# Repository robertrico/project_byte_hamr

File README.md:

# Byte Hamr

An open-source FPGA expansion card for the Apple II family of computers.

## Overview

Byte Hamr brings modern FPGA capabilities to the Apple II, II+, IIe, and IIgs. Unlike purpose-built cards that serve a single function, Byte Hamr is a general-purpose platform for developing and running custom hardware designs on vintage Apple hardware.

The card sits between the simplicity of the A2FPGA (which targets HDMI output) and the complexity of the Carte Blanche (which is difficult to obtain and uses proprietary tooling). Byte Hamr uses the Lattice ECP5 FPGA with full support for the open-source Yosys/nextpnr toolchain.

## Features

- Lattice ECP5-85F FPGA (84K LUTs, BGA381 package)
- 64MB SDRAM (AS4C32M16SB-7TCNTR)
- 128Mb SPI Flash for bitstream storage
- USB programming via FTDI FT231XQ
- JTAG header for development/debugging
- 20-pin GPIO header with heavy ground interleaving (Rev 2)
- 2×3 power breakout: +3V3, +5V, −5V, +12V, −12V (Rev 2)
- Full Apple II bus interface with bidirectional level shifting
- Dedicated FPGA-controlled data-bus transceiver OE (Rev 2)
- Hardware R/W inverter for correct transceiver direction (Rev 2)
- Bidirectional nRES — drive *and* monitor Apple II reset (Rev 2)
- Dual power input (USB or Apple II bus) with automatic switching
- On-board 100 MHz oscillator (Rev 2; 25 MHz on Rev 1)
- Open-source hardware and gateware

## Specifications

| Parameter | Value |
|-----------|-------|
| FPGA | Lattice ECP5-85F (LFE5U-85F-8BG381I) |
| Logic Elements | 84K LUTs |
| Block RAM | 3744 Kbit |
| SDRAM | 64MB, 16-bit bus |
| Flash | 128Mb SPI |
| USB | Full-speed via FT231XQ |
| GPIO | 20 pins, 3.3V LVCMOS33 |
| Oscillator | 100 MHz (Rev 2) |
| Power | +5V from USB or Apple II slot |
| Dimensions | Standard Apple II card form factor |

## Architecture

```
                                    +------------------+
                                    |     SDRAM        |
                                    |   (64MB x16)     |
                                    +--------+---------+
                                             |
+-------------+     +----------+     +-------+--------+     +----------+
| Apple II    |     | Level    |     |                |     |   SPI    |
| Expansion   +---->+ Shifters +---->+   ECP5-85F     +---->+  Flash   |
| Slot        |     | (5V/3.3V)|     |     FPGA       |     |  (16MB)  |
+-------------+     +----------+     +-------+--------+     +----------+
                                             |
                                     +-------+--------+
                                     |      USB       |
                                     |  (FT231XQ)     |
                                     +----------------+
```

## Power Distribution

Three on-board switching regulators generate the required voltages:

- +3.3V for FPGA I/O, SDRAM, Flash, level shifters
- +2.5V for FPGA auxiliary power
- +1.1V for FPGA core

Power can be sourced from USB (+5V) or the Apple II slot, with Schottky diode OR-ing for automatic switching. Rev 2 moves the 5V input diode ahead of the level-shifter rail so USB alone can power the bus logic.

## Bus Interface

Six 74LVC8T245 bidirectional level shifters translate between the Apple II's 5V bus and the FPGA's 3.3V I/O. The interface provides access to:

- 16-bit address bus
- 8-bit data bus (bidirectional)
- Control signals (R/W, PHI0, device select, etc.)

Rev 2 adds a dedicated 74AHC1G04 inverter (`U7`) that generates the correct-polarity DIR control for the data-bus transceiver, and exposes the transceiver's OE on an FPGA pin so gateware can cleanly gate drive.

## GPIO Header

20-pin header with ground interleaving (pin `1` marked at the top, `20` at the bottom). All pins are 3.3V LVCMOS33.

| GPIO | FPGA Site |   | GPIO | FPGA Site |
|------|-----------|---|------|-----------|
| GPIO_1  | P3 |   | GPIO_11 | J1 |
| GPIO_2  | P1 |   | GPIO_12 | H2 |
| GPIO_3  | P2 |   | GPIO_13 | H1 |
| GPIO_4  | N1 |   | GPIO_14 | G2 |
| GPIO_5  | M1 |   | GPIO_15 | G1 |
| GPIO_6  | L2 |   | GPIO_16 | F2 |
| GPIO_7  | L1 |   | GPIO_17 | F1 |
| GPIO_8  | K3 |   | GPIO_18 | E2 |
| GPIO_9  | K1 |   | GPIO_19 | E1 |
| GPIO_10 | K2 |   | GPIO_20 | D2 |

See [byte_hamr.lpf](gateware/rev2/constraints/byte_hamr.lpf) for full pin constraints.

## Project Status

**Rev 2** — fabricated and bring-up in progress (April 2026). Both boards enumerate over USB and pass initial SDRAM + GPIO tests.

**Rev 1** — sent to fabrication (December 2025). Tagged `rev1` in git; all Rev 1 gateware preserved under `gateware/rev1/`.

See [VERSION.md](VERSION.md) for full version history.

### Rev 2 changes

- Board footprint shrunk
- GPIO expanded from 12 → 20 pins with dense ground interleaving
- Power breakout block exposing ±5V / ±12V / 3V3
- On-board R/W inverter (replaces Rev 1 bodge wire)
- 5V diode moved ahead of level shifters so USB can power the bus side
- Shortened SDRAM routes to the ECP5
- Data-bus transceiver OE promoted from GPIO bodge to dedicated FPGA pin (`DATA_OE`, B20)
- Bidirectional nRES: separate `nRES_READ` input (A5) so gateware can monitor Apple II reset
- Oscillator upgraded 25 MHz → 100 MHz for better CDC oversampling and PLL headroom

## Repository Structure

```
project_byte_hamr/
├── hardware/
│   └── byte_hamr/          # Main FPGA card
│       ├── kicad/          # KiCad schematic and PCB
│       ├── bom/            # Bill of materials
│       └── gerbers/        # Manufacturing files
├── gateware/
│   ├── rev1/               # Rev 1 designs (frozen, matches rev1 git tag)
│   │   ├── constraints/
│   │   ├── signal_check/
│   │   ├── sdram_test/
│   │   ├── sdram_bank/
│   │   ├── pattern_rom/
│   │   ├── logic_hamr/
│   │   ├── smart_hamr/
│   │   ├── block_hamr/
│   │   └── flash_hamr/
│   └── rev2/               # Rev 2 designs (porting in progress)
│       ├── constraints/
│       └── signal_check/
├── software/
│   ├── ASM/                # 6502 assembly source (Merlin32)
│   ├── LOGICHAMR/          # Logic analyzer disk contents
│   └── utils/              # Disk image utilities
└── docs/                   # Documentation
```

## Getting Started

### Prerequisites

**Gateware:**
- [oss-cad-suite](https://github.com/YosysHQ/oss-cad-suite-build) (recommended) or individual tools:
  - [Yosys](https://github.com/YosysHQ/yosys) (synthesis)
  - [nextpnr-ecp5](https://github.com/YosysHQ/nextpnr) (place and route)
  - [openFPGALoader](https://github.com/trabucayre/openFPGALoader) (programming)

**6502 Assembly:**
- [Merlin32](https://brutaldeluxe.fr/products/crossdevtools/merlin/) (cross-assembler)

**Disk Utilities:**
- [AppleCommander](https://applecommander.github.io/) (disk image manipulation)
- [ADTPro](https://adtpro.com/) (disk transfer to real hardware)
- Java runtime

### Building Gateware

Builds are selected by `DESIGN` and `REV`. `REV` defaults to `rev1`; set `REV=rev2` when targeting the current hardware.

```bash
make                                # Build default (REV=rev1, DESIGN=signal_check)
make DESIGN=xxx                     # Build specific design (rev1)
make DESIGN=xxx REV=rev2            # Build against Rev 2 pinout
make sim DESIGN=xxx REV=rev2        # Run simulation
make wave                           # Run simulation and open GTKWave
make help                           # Show all available targets
```

`b8008_hamr` lives under `gateware/rev2/` and always needs `REV=rev2`; it also
needs `fusesoc` installed and a sibling `intel-8008-vhdl` checkout
(`INTEL8008_DIR`, default `~/Development/intel-8008-vhdl`) to generate its
netlist at build time, e.g. `make DESIGN=b8008_hamr REV=rev2 bit`.

### Programming

```bash
make DESIGN=xxx REV=rev2 prog                         # Program via JTAG (volatile)
make DESIGN=xxx REV=rev2 prog-flash                   # Program SPI flash (persistent)
make DESIGN=xxx REV=rev2 prog-flash SERIAL=<FTDI_SN>  # Target a specific board
```

### Software Development Workflow

```
┌─────────────┐     ┌───────────────┐     ┌─────────────┐     ┌───────────┐
│  Merlin32   │────▶│ AppleCommander│────▶│   ADTPro    │────▶│ Apple IIe │
│  (assemble) │     │ (create .dsk) │     │  (transfer) │     │   (run)   │
└─────────────┘     └───────────────┘     └─────────────┘     └───────────┘
```

```bash
# 1. Edit source in software/LOGICHAMR/*.S

# 2. Assemble with Merlin32
make assemble ASM_SRC=software/LOGICHAMR/LOGIC.S

# 3. Create disk image (auto-copied to ADTPro disks folder)
make create-dsk DSK=LOGICHAMR

# 4. Transfer via ADTPro to real hardware

# 5. On Apple II: BRUN LOGIC
```

**Disk utilities:**
```bash
make extract-dsk DSK=file.dsk     # Extract files from disk image
make list-dsk                     # List disks in ADTPro folder
```

### Utility Commands

```bash
make pinout             # Regenerate FPGA pinout from schematics
make lpf                # Regenerate LPF constraints
make clean              # Remove build files
```

## Gateware Designs

Rev 1 versions (proven on Rev 1 hardware):

| Design | Description |
|--------|-------------|
| [signal_check](gateware/rev1/signal_check/SIGNAL_CHECK.md) | Board bring-up test (SDRAM, GPIO, bus monitor) |
| sdram_test | Register-driven SDRAM access from Apple II |
| [sdram_bank](gateware/rev1/sdram_bank/README.md) | SDRAM bank-switching controller |
| [pattern_rom](gateware/rev1/pattern_rom/README.md) | SDRAM-backed pattern ROM for display testing |
| [logic_hamr](gateware/rev1/logic_hamr/README.md) | 8-channel logic analyzer with HIRES display |
| [smart_hamr](gateware/rev1/smart_hamr/README.md) | SmartPort/IWM disk controller with ESP32 companion |
| [block_hamr](gateware/rev1/block_hamr/README.md) | ProDOS block device with SDRAM and SPI flash persistence |
| [flash_hamr](gateware/rev1/flash_hamr/) | SD card ProDOS block device (PicoRV32 + FatFS) |

Rev 2 port: `signal_check` ported and validated; other designs pending.

## Testing

Bringup sequence for new boards:

1. Visual inspection
2. Power rail verification (+5V, +3.3V, +2.5V, +1.1V)
3. USB enumeration (FTDI detection)
4. FPGA configuration with [signal_check](gateware/rev2/signal_check/)
5. Oscillator verification (100 MHz on scope; derived 25 MHz appears on SDRAM_CLK)
6. GPIO walk — watch walking 1s across `GPIO_9`..`GPIO_20`
7. Apple II bus communication (register loopback at $C0C0)
8. Data-bus transceiver + R/W inverter walk: `C0C0:01 → C0C0`, then `02`, `04`, … `80`
9. Full system integration

## Design References

This project builds on the work of others:

- [ULX3S](https://github.com/emard/ulx3s) - ECP5 reference design, power architecture
- [Xander's 8-bit fun](https://xjmaas.wordpress.com/my-apple-collection/apple-edge-connector-template-for-eagle/) - Apple II Edge Card Design
- [Understanding the Apple IIe](https://archive.org/details/understanding_the_apple_iie) - Jim Sather's essential reference

## Why "Byte Hamr"?

"Hamr" is Old Norse for "shape" or "form" — the concept of shapeshifting in Norse mythology. Byte Hamr: shapeshifting bytes. An FPGA that can become any hardware you define. The shape changes based on what you program it to be.

## License

This project is released under the [MIT License](LICENSE.md).

## Author

Robert Rico

## Contributing

This is an early-stage project. Issues, suggestions, and pull requests welcome.

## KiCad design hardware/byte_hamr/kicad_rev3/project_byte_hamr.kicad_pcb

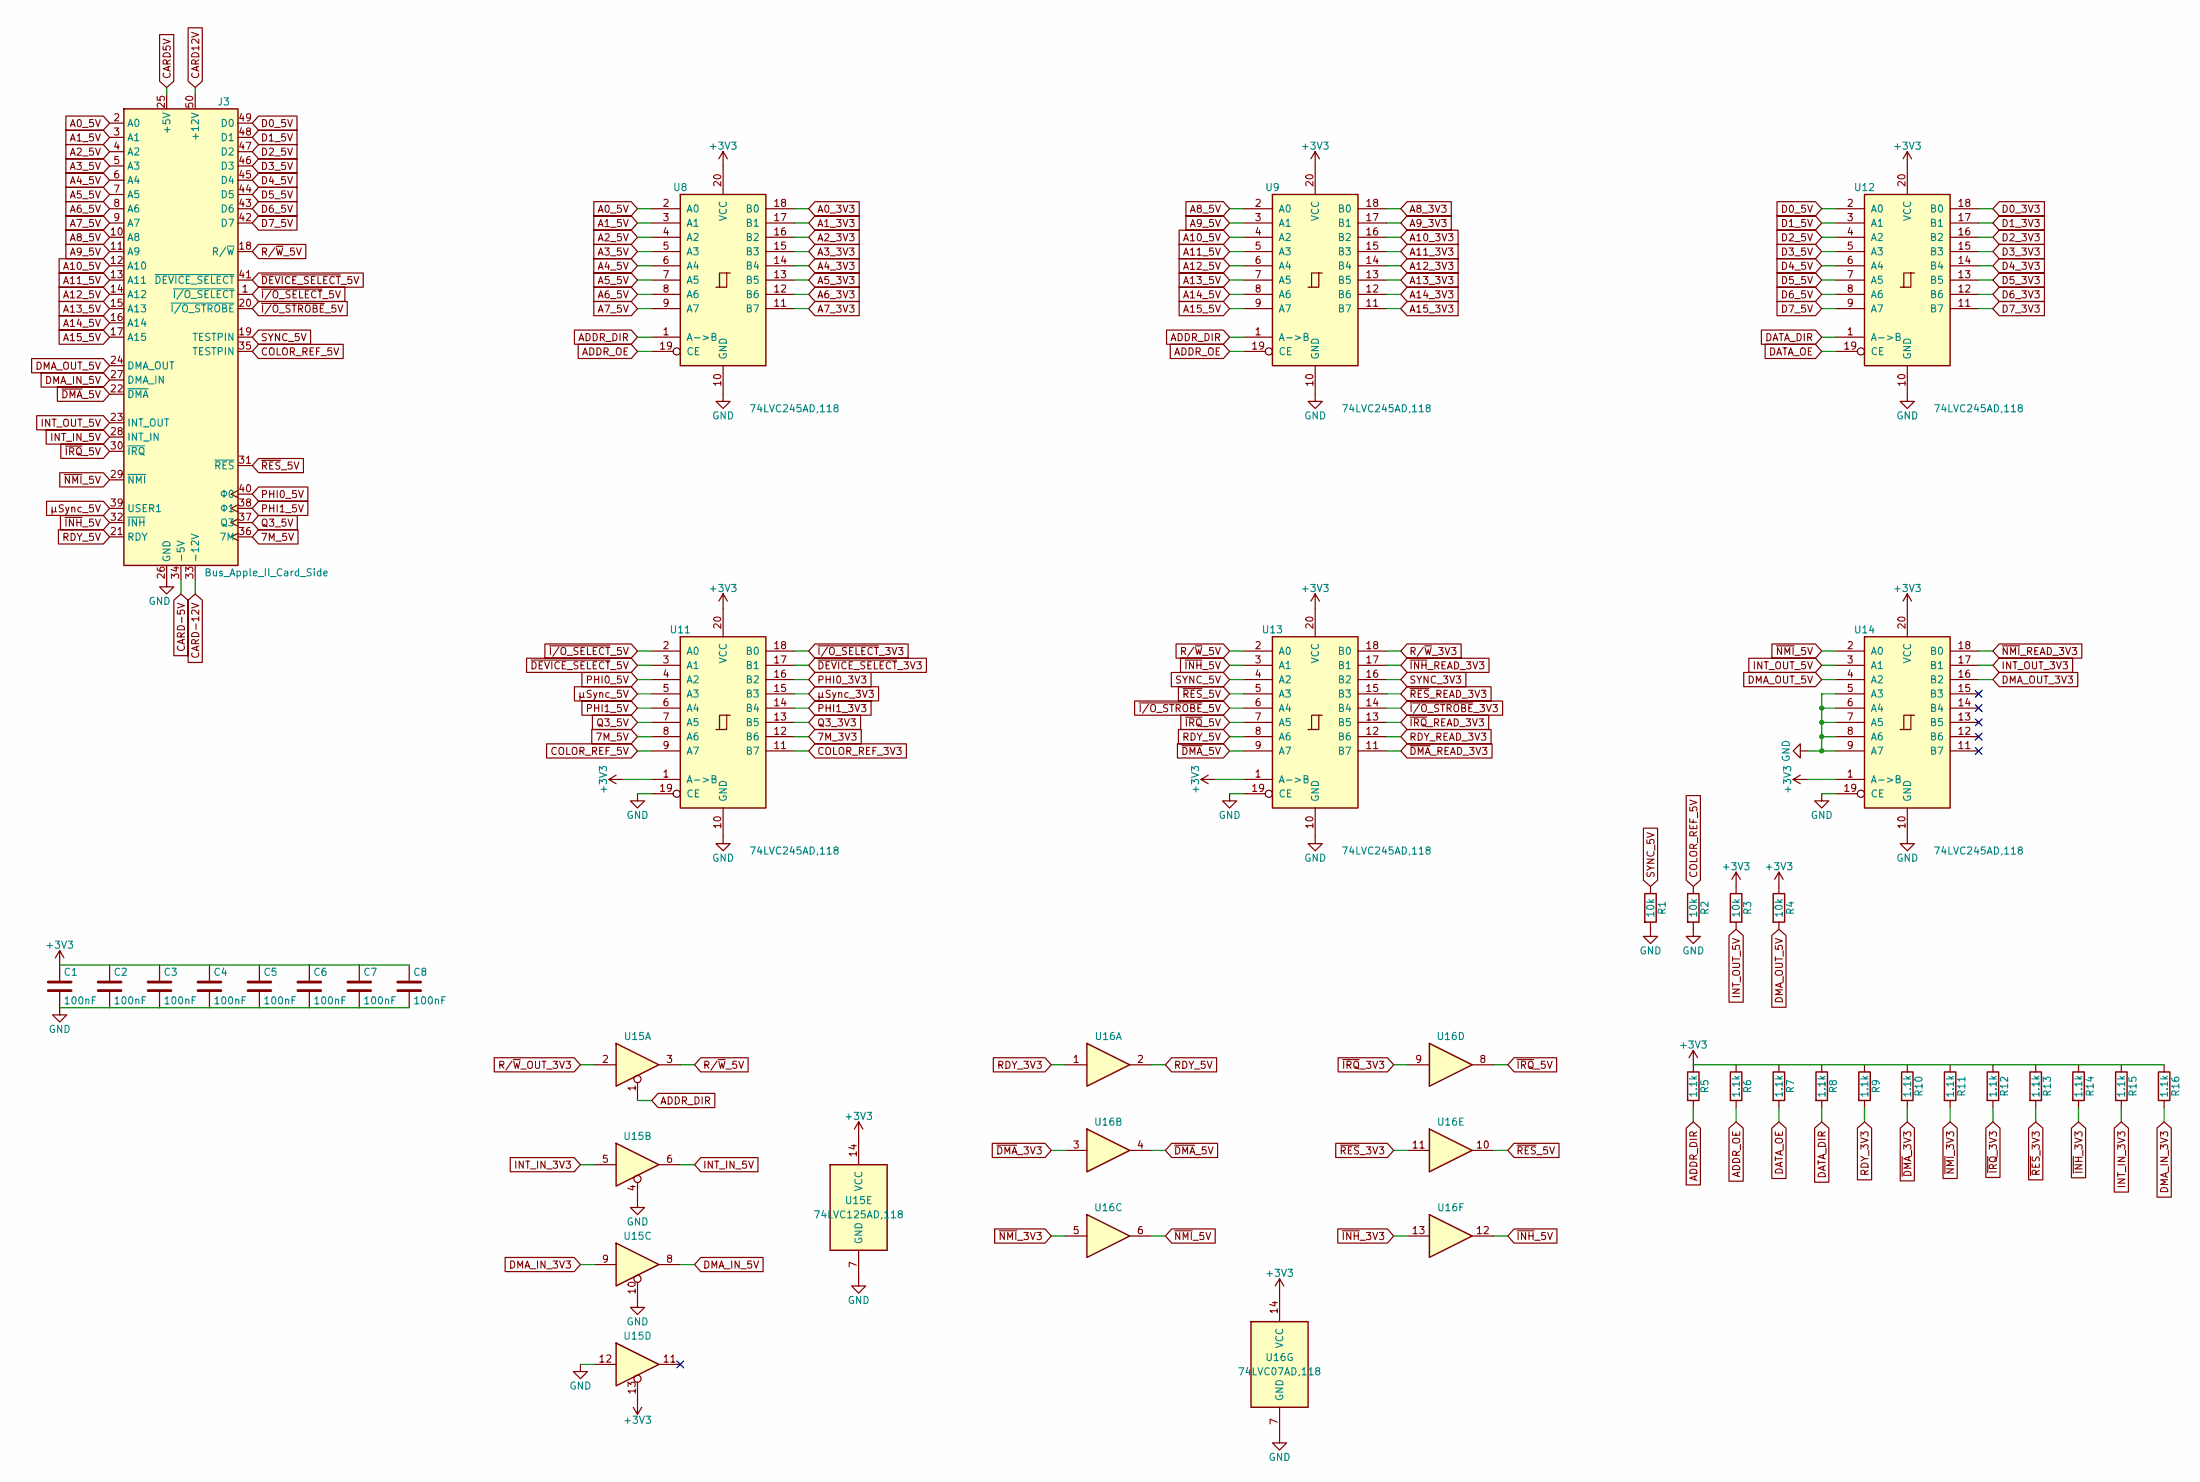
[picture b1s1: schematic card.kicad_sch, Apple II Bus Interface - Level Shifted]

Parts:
C1, C2, C3, C4, C5, C6, C7, C8: 100nF; C_1206_3216Metric; MPN CL31B104KBCNNNC; DigiKey 1276-1017-1-ND
J3: Bus_Apple_II_Card_Side; Peripheral_Bus_Edge
R1, R2, R3, R4: 10k; R_1206_3216Metric; MPN RMCF1206FT10K0; DigiKey RMCF1206FT10K0CT-ND
R5, R6, R7, R8, R9, R10, R11, R12, R13, R14, R15, R16: 1.1k; R_1206_3216Metric; MPN RMCF1206FT1K10; DigiKey 738-RMCF1206FT1K10CT-ND
U8, U9, U11, U12, U13, U14: 74LVC245AD,118; SOIC-20W_7.5x12.8mm_P1.27mm; MPN 74LVC245AD,118; DigiKey 1727-3104-1-ND
U15: 74LVC125AD,118; SOIC-14_3.9x8.7mm_P1.27mm; MPN 74LVC125AD,118; DigiKey 1727-3091-1-ND
U16: 74LVC07AD,118; SOIC-14_3.9x8.7mm_P1.27mm; MPN 74LVC07AD,118; DigiKey 1727-3089-1-ND

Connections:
7M_3V3: U11.12 (B6); also elsewhere on the board
7M_5V: J3.36 (7M), U11.8 (A6)
+3V3: C1.1, C2.1, C3.1, C4.1, C5.1, C6.1, C7.1, C8.1, R3.1, R4.1, R5.1, R6.1, R7.1, R8.1, R9.1, R10.1, R11.1, R12.1, R13.1, R14.1, R15.1, R16.1, U8.20 (VCC), U9.20 (VCC), U11.1 (A->B), U11.20 (VCC), U12.20 (VCC), U13.1 (A->B), U13.20 (VCC), U14.1 (A->B), U14.20 (VCC), U15.13, U15.14 (VCC), U16.14 (VCC); also elsewhere on the board
A0_3V3: U8.18 (B0); also elsewhere on the board
A0_5V: J3.2 (A0), U8.2 (A0)
A1_3V3: U8.17 (B1); also elsewhere on the board
A1_5V: J3.3 (A1), U8.3 (A1)
A2_3V3: U8.16 (B2); also elsewhere on the board
A2_5V: J3.4 (A2), U8.4 (A2)
A3_3V3: U8.15 (B3); also elsewhere on the board
A3_5V: J3.5 (A3), U8.5 (A3)
A4_3V3: U8.14 (B4); also elsewhere on the board
A4_5V: J3.6 (A4), U8.6 (A4)
A5_3V3: U8.13 (B5); also elsewhere on the board
A5_5V: J3.7 (A5), U8.7 (A5)
A6_3V3: U8.12 (B6); also elsewhere on the board
A6_5V: J3.8 (A6), U8.8 (A6)
A7_3V3: U8.11 (B7); also elsewhere on the board
A7_5V: J3.9 (A7), U8.9 (A7)
A8_3V3: U9.18 (B0); also elsewhere on the board
A8_5V: J3.10 (A8), U9.2 (A0)
A9_3V3: U9.17 (B1); also elsewhere on the board
A9_5V: J3.11 (A9), U9.3 (A1)
A10_3V3: U9.16 (B2); also elsewhere on the board
A10_5V: J3.12 (A10), U9.4 (A2)
A11_3V3: U9.15 (B3); also elsewhere on the board
A11_5V: J3.13 (A11), U9.5 (A3)
A12_3V3: U9.14 (B4); also elsewhere on the board
A12_5V: J3.14 (A12), U9.6 (A4)
A13_3V3: U9.13 (B5); also elsewhere on the board
A13_5V: J3.15 (A13), U9.7 (A5)
A14_3V3: U9.12 (B6); also elsewhere on the board
A14_5V: J3.16 (A14), U9.8 (A6)
A15_3V3: U9.11 (B7); also elsewhere on the board
A15_5V: J3.17 (A15), U9.9 (A7)
ADDR_DIR: R5.2, U8.1 (A->B), U9.1 (A->B), U15.1; also elsewhere on the board
ADDR_OE: R6.2, U8.19 (CE), U9.19 (CE); also elsewhere on the board
CARD5V: J3.25 (+5V); also elsewhere on the board
CARD12V: J3.50 (+12V); also elsewhere on the board
CARD-5V: J3.34 (-5V); also elsewhere on the board
CARD-12V: J3.33 (-12V); also elsewhere on the board
COLOR_REF_3V3: U11.11 (B7); also elsewhere on the board
COLOR_REF_5V: J3.35 (TESTPIN), R2.1, U11.9 (A7)
D0_3V3: U12.18 (B0); also elsewhere on the board
D0_5V: J3.49 (D0), U12.2 (A0)
D1_3V3: U12.17 (B1); also elsewhere on the board
D1_5V: J3.48 (D1), U12.3 (A1)
D2_3V3: U12.16 (B2); also elsewhere on the board
D2_5V: J3.47 (D2), U12.4 (A2)
D3_3V3: U12.15 (B3); also elsewhere on the board
D3_5V: J3.46 (D3), U12.5 (A3)
D4_3V3: U12.14 (B4); also elsewhere on the board
D4_5V: J3.45 (D4), U12.6 (A4)
D5_3V3: U12.13 (B5); also elsewhere on the board
D5_5V: J3.44 (D5), U12.7 (A5)
D6_3V3: U12.12 (B6); also elsewhere on the board
D6_5V: J3.43 (D6), U12.8 (A6)
D7_3V3: U12.11 (B7); also elsewhere on the board
D7_5V: J3.42 (D7), U12.9 (A7)
DATA_DIR: R8.2, U12.1 (A->B); also elsewhere on the board
DATA_OE: R7.2, U12.19 (CE); also elsewhere on the board
DMA_IN_3V3: R16.2, U15.9; also elsewhere on the board
DMA_IN_5V: J3.27 (DMA_IN), U15.8
DMA_OUT_3V3: U14.16 (B2); also elsewhere on the board
DMA_OUT_5V: J3.24 (DMA_OUT), R4.2, U14.4 (A2)
GND: C1.2, C2.2, C3.2, C4.2, C5.2, C6.2, C7.2, C8.2, J3.26 (GND), R1.2, R2.2, U8.10 (GND), U9.10 (GND), U11.10 (GND), U11.19 (CE), U12.10 (GND), U13.10 (GND), U13.19 (CE), U14.5 (A3), U14.6 (A4), U14.7 (A5), U14.8 (A6), U14.9 (A7), U14.10 (GND), U14.19 (CE), U15.4, U15.7 (GND), U15.10, U15.12, U16.7 (GND); also elsewhere on the board
INT_IN_3V3: R15.2, U15.5; also elsewhere on the board
INT_IN_5V: J3.28 (INT_IN), U15.6
INT_OUT_3V3: U14.17 (B1); also elsewhere on the board
INT_OUT_5V: J3.23 (INT_OUT), R3.2, U14.3 (A1)
PHI0_3V3: U11.16 (B2); also elsewhere on the board
PHI0_5V: J3.40 (Φ0), U11.4 (A2)
PHI1_3V3: U11.14 (B4); also elsewhere on the board
PHI1_5V: J3.38 (Φ1), U11.6 (A4)
Q3_3V3: U11.13 (B5); also elsewhere on the board
Q3_5V: J3.37 (Q3), U11.7 (A5)
RDY_3V3: R9.2, U16.1; also elsewhere on the board
RDY_5V: J3.21 (RDY), U13.8 (A6), U16.2
RDY_READ_3V3: U13.12 (B6); also elsewhere on the board
R/~W_3V3: U13.18 (B0); also elsewhere on the board
R/~W_5V: J3.18 (R/~W), U13.2 (A0), U15.3
R/~W_OUT_3V3: U15.2; also elsewhere on the board
SYNC_3V3: U13.16 (B2); also elsewhere on the board
SYNC_5V: J3.19 (TESTPIN), R1.1, U13.4 (A2)
~DEVICE_SELECT_3V3: U11.17 (B1); also elsewhere on the board
~DEVICE_SELECT_5V: J3.41 (~DEVICE_SELECT), U11.3 (A1)
~DMA_3V3: R10.2, U16.3; also elsewhere on the board
~DMA_5V: J3.22 (~DMA), U13.9 (A7), U16.4
~DMA_READ_3V3: U13.11 (B7); also elsewhere on the board
~INH_3V3: R14.2, U16.13; also elsewhere on the board
~INH_5V: J3.32 (~INH), U13.3 (A1), U16.12
~INH_READ_3V3: U13.17 (B1); also elsewhere on the board
~IRQ_3V3: R12.2, U16.9; also elsewhere on the board
~IRQ_5V: J3.30 (~IRQ), U13.7 (A5), U16.8
~IRQ_READ_3V3: U13.13 (B5); also elsewhere on the board
~I/O_SELECT_3V3: U11.18 (B0); also elsewhere on the board
~I/O_SELECT_5V: J3.1 (~I/O_SELECT), U11.2 (A0)
~I/O_STROBE_3V3: U13.14 (B4); also elsewhere on the board
~I/O_STROBE_5V: J3.20 (~I/O_STROBE), U13.6 (A4)
~NMI_3V3: R11.2, U16.5; also elsewhere on the board
~NMI_5V: J3.29 (~NMI), U14.2 (A0), U16.6
~NMI_READ_3V3: U14.18 (B0); also elsewhere on the board
~RES_3V3: R13.2, U16.11; also elsewhere on the board
~RES_5V: J3.31 (~RES), U13.5 (A3), U16.10
~RES_READ_3V3: U13.15 (B3); also elsewhere on the board
µSync_3V3: U11.15 (B3); also elsewhere on the board
µSync_5V: J3.39 (USER1), U11.5 (A3)

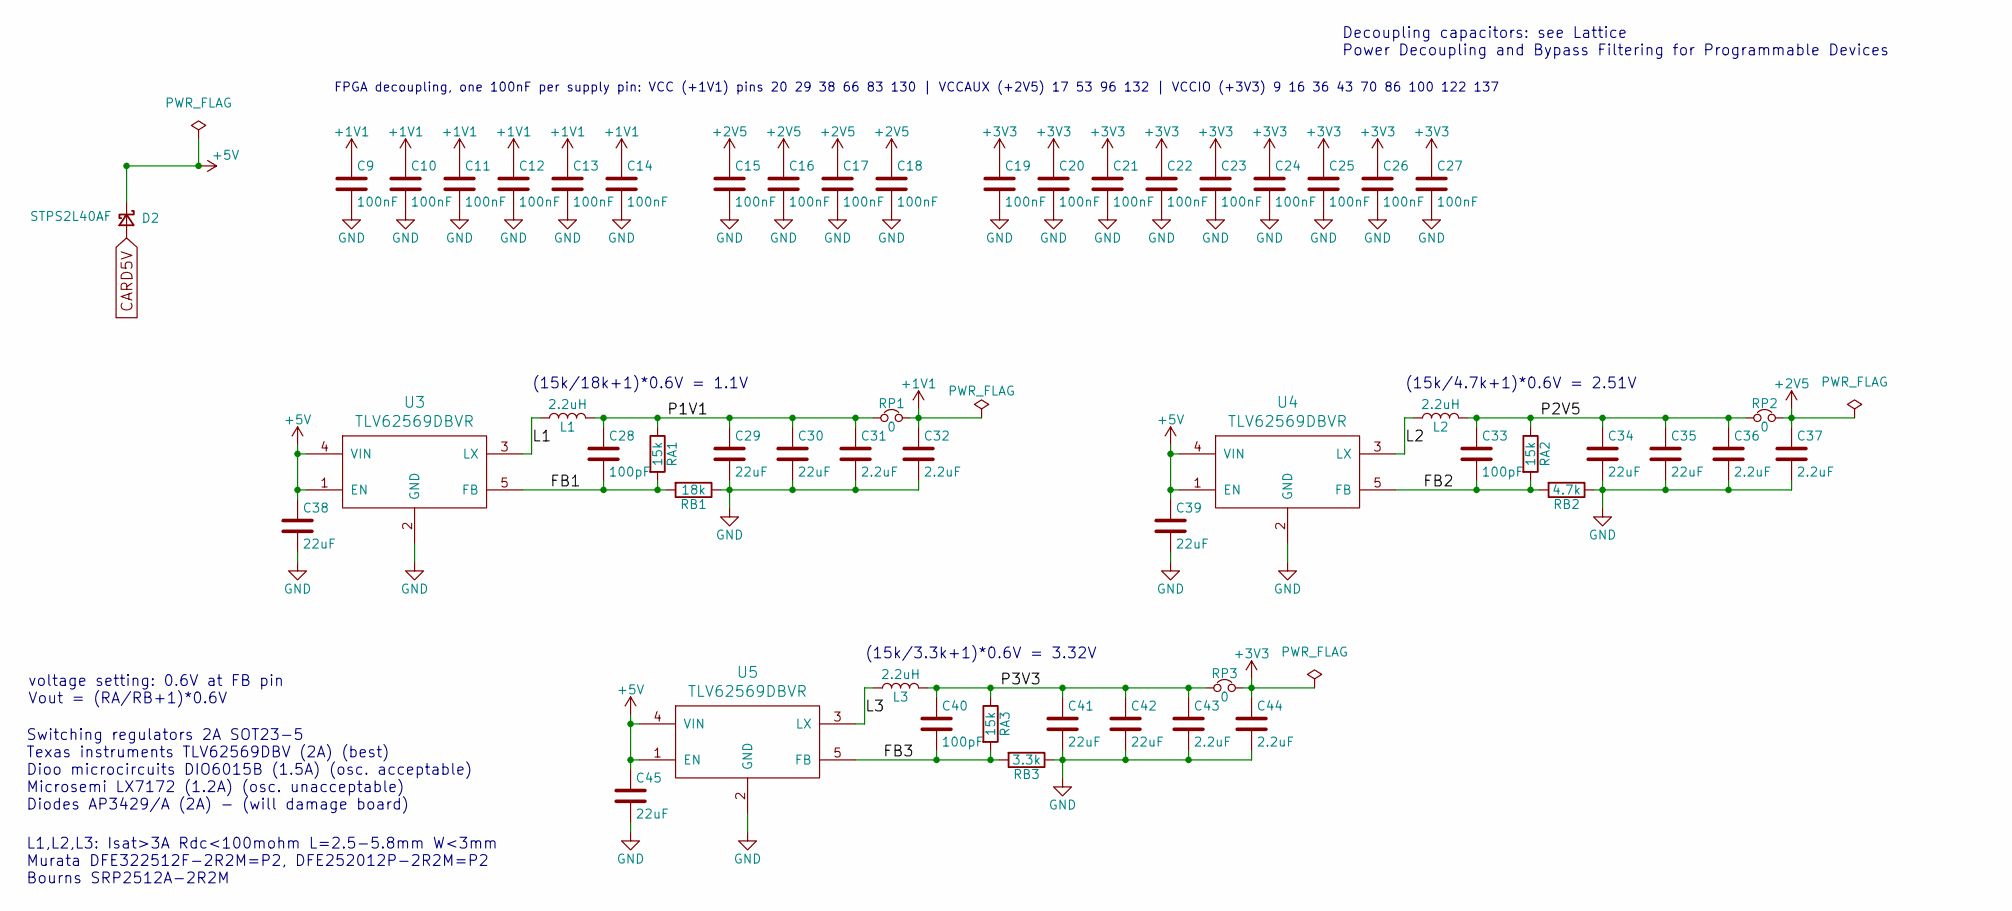
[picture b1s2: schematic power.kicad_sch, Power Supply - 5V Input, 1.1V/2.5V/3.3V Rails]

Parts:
C9, C10, C11, C12, C13, C14, C15, C16, C17, C18, C19, C20, C21, C22, C23, C24, C25, C26, C27: 100nF; C_1206_3216Metric; MPN CL31B104KBCNNNC; DigiKey 1276-1017-1-ND
C28, C33, C40: 100pF; C_1206_3216Metric; MPN 885012008043; DigiKey 732-7887-1-ND
C29, C30, C34, C35, C38, C39, C41, C42, C45: 22uF; C_1206_3216Metric; MPN CL31A226MOHNNNE; DigiKey 1276-3050-1-ND
C31, C32, C36, C37, C43, C44: 2.2uF; C_1206_3216Metric; MPN CL31B225KOHNNNE; DigiKey 1276-1264-1-ND
D2: STPS2L40AF; D_SMA; MPN STPS2L40AF; DigiKey 497-18870-1-ND
L1, L2, L3: 2.2uH; L_1008_1210; MPN DFE322520F-2R2M=P2; DigiKey 490-DFE322520F-2R2M=P2CT-ND
RA1, RA2, RA3: 15k; R_1206_3216Metric; MPN RMCF1206FT15K0; DigiKey RMCF1206FT15K0CT-ND
RB1: 18k; R_1206_3216Metric; MPN CR1206-FX-1802ELF; DigiKey CR1206-FX-1802ELFCT-ND
RB2: 4.7k; R_1206_3216Metric; MPN RMCF1206FT4K70; DigiKey RMCF1206FT4K70CT-ND
RB3: 3.3k; R_1206_3216Metric; MPN RMCF1206FT3K30; DigiKey RMCF1206FT3K30CT-ND
RP1, RP2, RP3: 0; R_1206_3216Metric; MPN RMCF1206ZT0R00; DigiKey RMCF1206ZT0R00CT-ND
U3, U4, U5: TLV62569DBVR; TSOT-25; MPN TLV62569DBVR; DigiKey 296-47360-1-ND

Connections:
+1V1: C9.1, C10.1, C11.1, C12.1, C13.1, C14.1, C32.1, RP1.2; also elsewhere on the board
+2V5: C15.1, C16.1, C17.1, C18.1, C37.1, RP2.2; also elsewhere on the board
+3V3: C19.1, C20.1, C21.1, C22.1, C23.1, C24.1, C25.1, C26.1, C27.1, C44.1, RP3.2; also elsewhere on the board
+5V: C38.1, C39.1, C45.1, D2.1 (K), U3.1 (EN), U3.4 (VIN), U4.1 (EN), U4.4 (VIN), U5.1 (EN), U5.4 (VIN)
/power/FB1: C28.2, RA1.2, RB1.2, U3.5 (FB)
/power/FB2: C33.2, RA2.2, RB2.2, U4.5 (FB)
/power/FB3: C40.2, RA3.2, RB3.2, U5.5 (FB)
/power/L1: L1.1, U3.3 (LX)
/power/L2: L2.1, U4.3 (LX)
/power/L3: L3.1, U5.3 (LX)
/power/P1V1: C28.1, C29.1, C30.1, C31.1, L1.2, RA1.1, RP1.1
/power/P2V5: C33.1, C34.1, C35.1, C36.1, L2.2, RA2.1, RP2.1
/power/P3V3: C40.1, C41.1, C42.1, C43.1, L3.2, RA3.1, RP3.1
CARD5V: D2.2 (A); also elsewhere on the board
GND: C9.2, C10.2, C11.2, C12.2, C13.2, C14.2, C15.2, C16.2, C17.2, C18.2, C19.2, C20.2, C21.2, C22.2, C23.2, C24.2, C25.2, C26.2, C27.2, C29.2, C30.2, C31.2, C32.2, C34.2, C35.2, C36.2, C37.2, C38.2, C39.2, C41.2, C42.2, C43.2, C44.2, C45.2, RB1.1, RB2.1, RB3.1, U3.2 (GND), U4.2 (GND), U5.2 (GND); also elsewhere on the board

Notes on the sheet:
Switching regulators 2A SOT23-5 Texas instruments TLV62569DBV (2A) (best) Dioo microcircuits DIO6015B (1.5A) (osc. acceptable) Microsemi LX7172 (1.2A) (osc. unacceptable) Diodes AP3429/A (2A) - (will damage board)
(15k/18k+1)*0.6V = 1.1V
L1,L2,L3: Isat>3A Rdc<100mohm L=2.5-5.8mm W<3mm Murata DFE322512F-2R2M=P2, DFE252012P-2R2M=P2 Bourns SRP2512A-2R2M
(15k/4.7k+1)*0.6V = 2.51V
(15k/3.3k+1)*0.6V = 3.32V
Decoupling capacitors: see Lattice Power Decoupling and Bypass Filtering for Programmable Devices
voltage setting: 0.6V at FB pin Vout = (RA/RB+1)*0.6V
FPGA decoupling, one 100nF per supply pin: VCC (+1V1) pins 20 29 38 66 83 130 | VCCAUX (+2V5) 17 53 96 132 | VCCIO (+3V3) 9 16 36 43 70 86 100 122 137

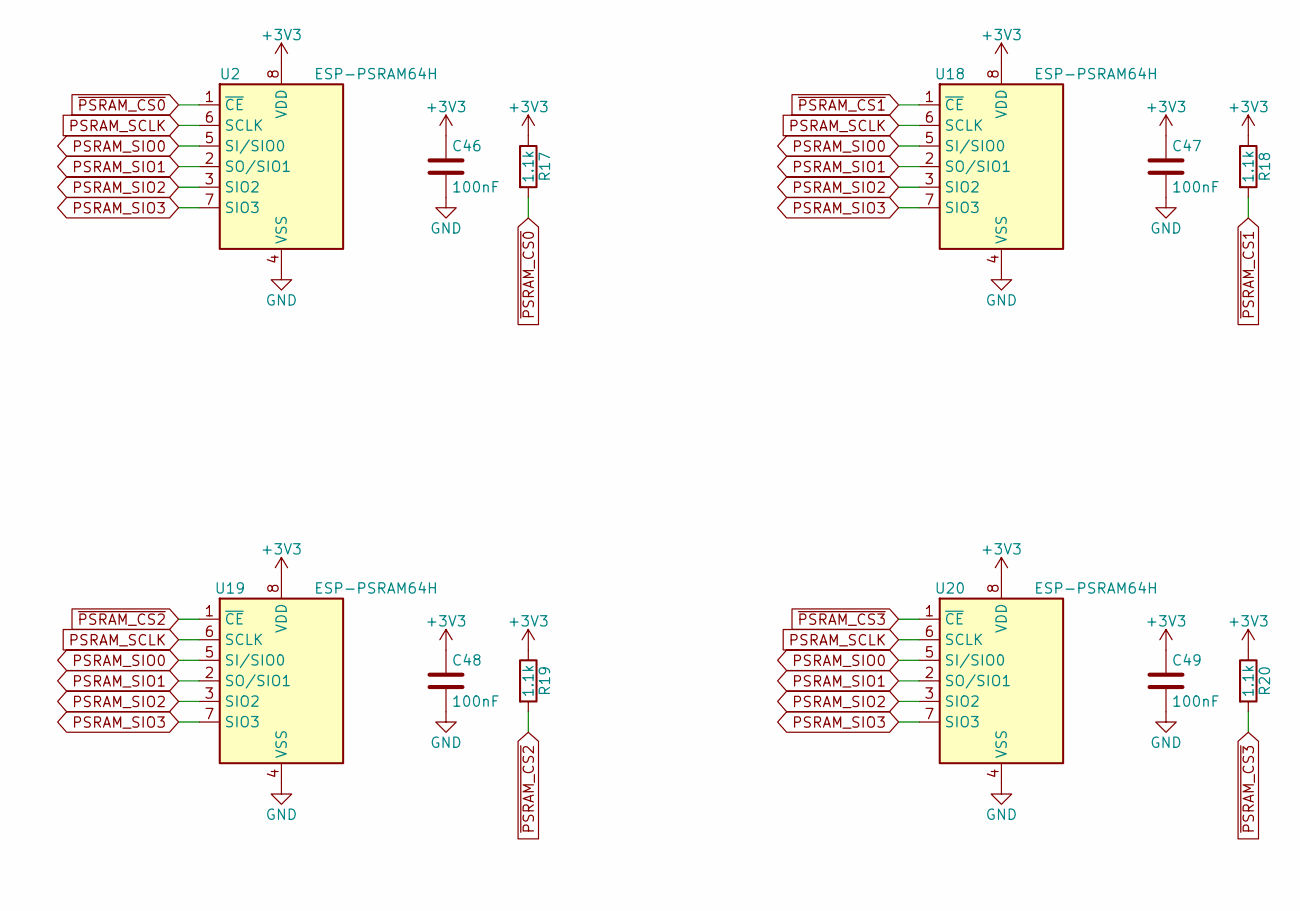
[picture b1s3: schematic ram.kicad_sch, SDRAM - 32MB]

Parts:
C46, C47, C48, C49: 100nF; C_1206_3216Metric; MPN CL31B104KBCNNNC; DigiKey 1276-1017-1-ND
R17, R18, R19, R20: 1.1k; R_1206_3216Metric; MPN RMCF1206FT1K10; DigiKey 738-RMCF1206FT1K10CT-ND
U2, U18, U19, U20: ESP-PSRAM64H; SOIC-8_3.9x4.9mm_P1.27mm; MPN ESP-PSRAM64H; DigiKey 1528-4677-ND

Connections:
+3V3: C46.1, C47.1, C48.1, C49.1, R17.1, R18.1, R19.1, R20.1, U2.8 (VDD), U18.8 (VDD), U19.8 (VDD), U20.8 (VDD); also elsewhere on the board
GND: C46.2, C47.2, C48.2, C49.2, U2.4 (VSS), U18.4 (VSS), U19.4 (VSS), U20.4 (VSS); also elsewhere on the board
PSRAM_SCLK: U2.6 (SCLK), U18.6 (SCLK), U19.6 (SCLK), U20.6 (SCLK); also elsewhere on the board
PSRAM_SIO0: U2.5 (SI/SIO0), U18.5 (SI/SIO0), U19.5 (SI/SIO0), U20.5 (SI/SIO0); also elsewhere on the board
PSRAM_SIO1: U2.2 (SO/SIO1), U18.2 (SO/SIO1), U19.2 (SO/SIO1), U20.2 (SO/SIO1); also elsewhere on the board
PSRAM_SIO2: U2.3 (SIO2), U18.3 (SIO2), U19.3 (SIO2), U20.3 (SIO2); also elsewhere on the board
PSRAM_SIO3: U2.7 (SIO3), U18.7 (SIO3), U19.7 (SIO3), U20.7 (SIO3); also elsewhere on the board
~PSRAM_CS0: R17.2, U2.1 (~CE); also elsewhere on the board
~PSRAM_CS1: R18.2, U18.1 (~CE); also elsewhere on the board
~PSRAM_CS2: R19.2, U19.1 (~CE); also elsewhere on the board
~PSRAM_CS3: R20.2, U20.1 (~CE); also elsewhere on the board
